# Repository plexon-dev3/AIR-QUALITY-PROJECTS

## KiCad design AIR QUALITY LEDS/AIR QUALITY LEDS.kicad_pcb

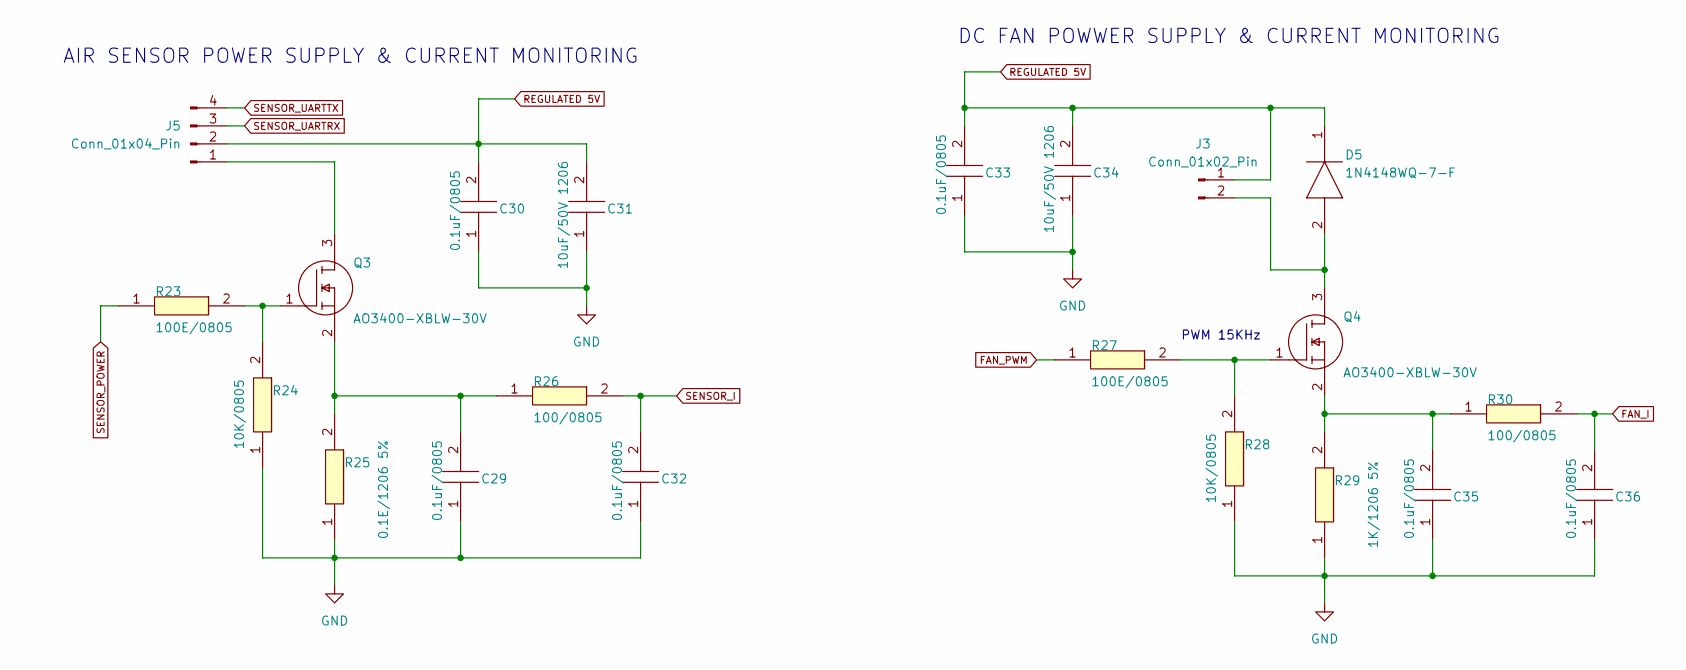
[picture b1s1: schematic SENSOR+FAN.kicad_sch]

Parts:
C29, C30, C32, C33, C35, C36: 0.1uF/0805; C_0805_2012Metric; MANUFACTURER_PART_NUMBER C0805C100F1GACAUTO
C31, C34: 10uF/50V 1206; C_1206_3216Metric; MANUFACTURER_PART_NUMBER C1206C221F5GACAUTO; MOUSER PART NUMBER 80-C1206C221F5GAUTO
D5: 1N4148WQ-7-F; SOD3716X145N; MANUFACTURER_PART_NUMBER 1N4148WQ-7-F; MOUSER PART NUMBER 621-1N4148WQ-7-F
J3: Conn_01x02_Pin; PinSocket_1x02_P2.54mm_Vertical
J5: Conn_01x04_Pin; Hirose_DF13-04P-1.25DSA_1x04_P1.25mm_Vertical
Q3, Q4: AO3400-XBLW-30V; SOT95P237X112-3N; MANUFACTURER_PART_NUMBER IRLML6344TRPBF; MOUSER PART NUMBER 942-IRLML6344TRPBF
R23, R27: 100E/0805; R_0805_2012Metric; MANUFACTURER_PART_NUMBER CMP0805QFX-1001ELF; MOUSER PART NUMBER 652-CMP0805QFX-1001E
R24, R28: 10K/0805; R_0805_2012Metric; MANUFACTURER_PART_NUMBER CMP0805QFX-1001ELF; MOUSER PART NUMBER 652-CMP0805QFX-1001E
R25: 0.1E/1206 5%; R_1206_3216Metric; MANUFACTURER_PART_NUMBER CR1206-FX-16R2ELF; MOUSER PART NUMBER 652-CR1206FX-16R2ELF
R26, R30: 100/0805; R_0805_2012Metric; MANUFACTURER_PART_NUMBER CMP0805QFX-1001ELF; MOUSER PART NUMBER 652-CMP0805QFX-1001E
R29: 1K/1206 5%; R_1206_3216Metric; MANUFACTURER_PART_NUMBER CR1206-FX-16R2ELF; MOUSER PART NUMBER 652-CR1206FX-16R2ELF

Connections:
FAN_I: C36.2, R30.2; also elsewhere on the board
FAN_PWM: R27.1; also elsewhere on the board
GND: C29.1, C30.1, C31.1, C32.1, C33.1, C34.1, C35.1, C36.1, R24.1, R25.1, R28.1, R29.1; also elsewhere on the board
unnamed: D5.2 (A), J3.2, Q4.3 (D)
unnamed: J5.1, Q3.3 (D)
unnamed: Q3.1 (G), R23.2, R24.2
unnamed: C29.2, Q3.2 (S), R25.2, R26.1
unnamed: Q4.1 (G), R27.2, R28.2
unnamed: C35.2, Q4.2 (S), R29.2, R30.1
REGULATED 5V: C30.2, C31.2, C33.2, C34.2, D5.1 (K), J3.1, J5.2; also elsewhere on the board
SENSOR_I: C32.2, R26.2; also elsewhere on the board
SENSOR_POWER: R23.1; also elsewhere on the board
SENSOR_UARTRX: J5.3; also elsewhere on the board
SENSOR_UARTTX: J5.4; also elsewhere on the board

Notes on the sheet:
AIR SENSOR POWER SUPPLY & CURRENT MONITORING
DC FAN POWWER SUPPLY & CURRENT MONITORING
PWM 15KHz

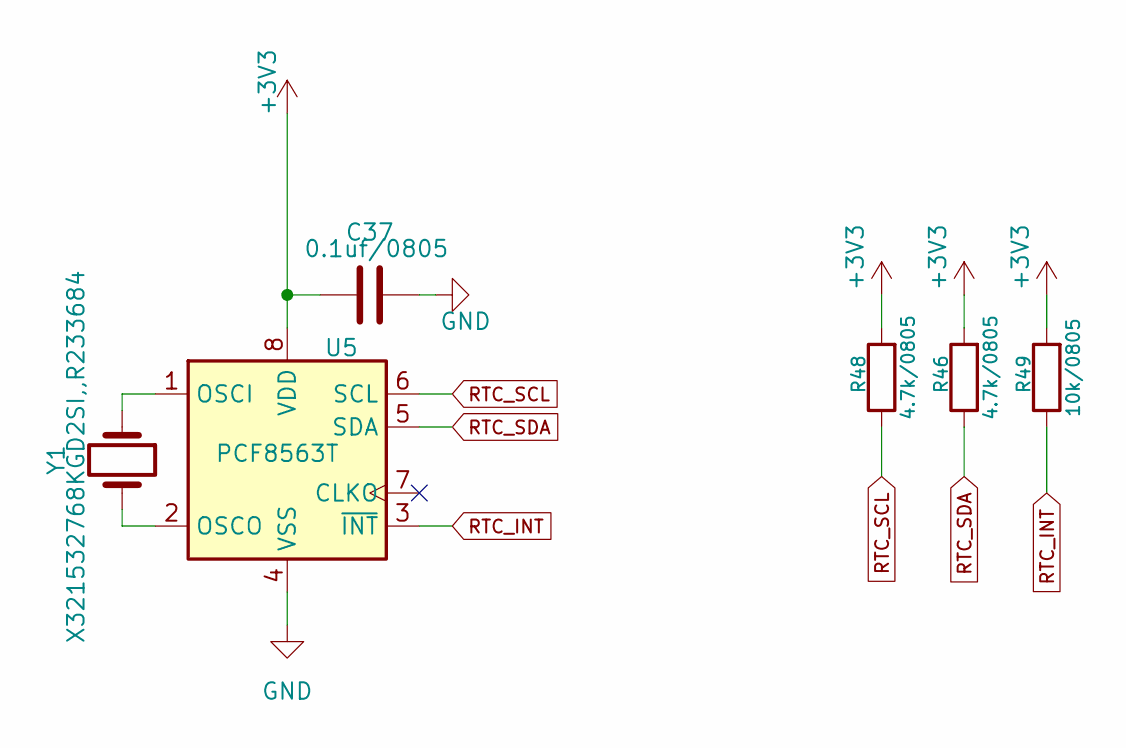
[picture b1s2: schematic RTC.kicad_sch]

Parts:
C37: 0.1uf/0805; C_0805_2012Metric
R46, R48: 4.7k/0805; R_0805_2012Metric
R49: 10k/0805; R_0805_2012Metric
U5: PCF8563T; SO-8_3.9x4.9mm_P1.27mm
Y1: X321532768KGD2SI,,R233684; Crystal_SMD_MicroCrystal_CC7V-T1A-2Pin_3.2x1.5mm

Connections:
+3V3: C37.1, R46.2, R48.2, R49.2, U5.8 (VDD); also elsewhere on the board
GND: C37.2, U5.4 (VSS); also elsewhere on the board
unnamed: U5.1 (OSCI), Y1.1
unnamed: U5.2 (OSCO), Y1.2
RTC_INT: R49.1, U5.3 (~INT); also elsewhere on the board
RTC_SCL: R48.1, U5.6 (SCL); also elsewhere on the board
RTC_SDA: R46.1, U5.5 (SDA); also elsewhere on the board

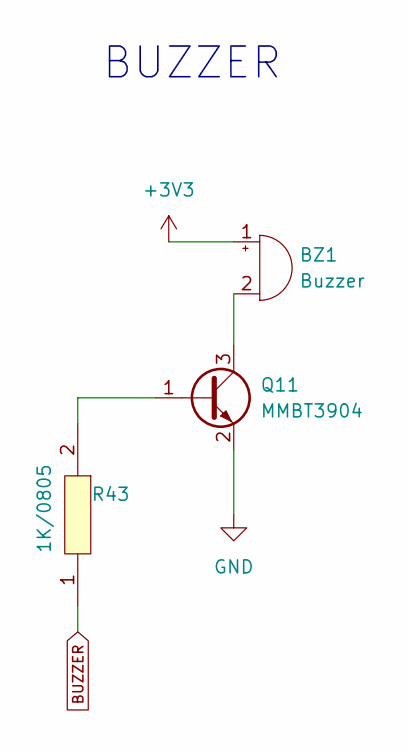
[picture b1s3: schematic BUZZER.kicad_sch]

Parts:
BZ1: Buzzer; Buzzer_12x9.5RM7.6
Q11: MMBT3904; SOT-23
R43: 1K/0805; R_0805_2012Metric; MANUFACTURER_PART_NUMBER CMP0805QFX-1001ELF; MOUSER PART NUMBER 652-CMP0805QFX-1001E

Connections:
+3V3: BZ1.1 (+); also elsewhere on the board
BUZZER: R43.1; also elsewhere on the board
GND: Q11.2 (E); also elsewhere on the board
unnamed: BZ1.2 (-), Q11.3 (C)
unnamed: Q11.1 (B), R43.2

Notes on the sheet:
BUZZER

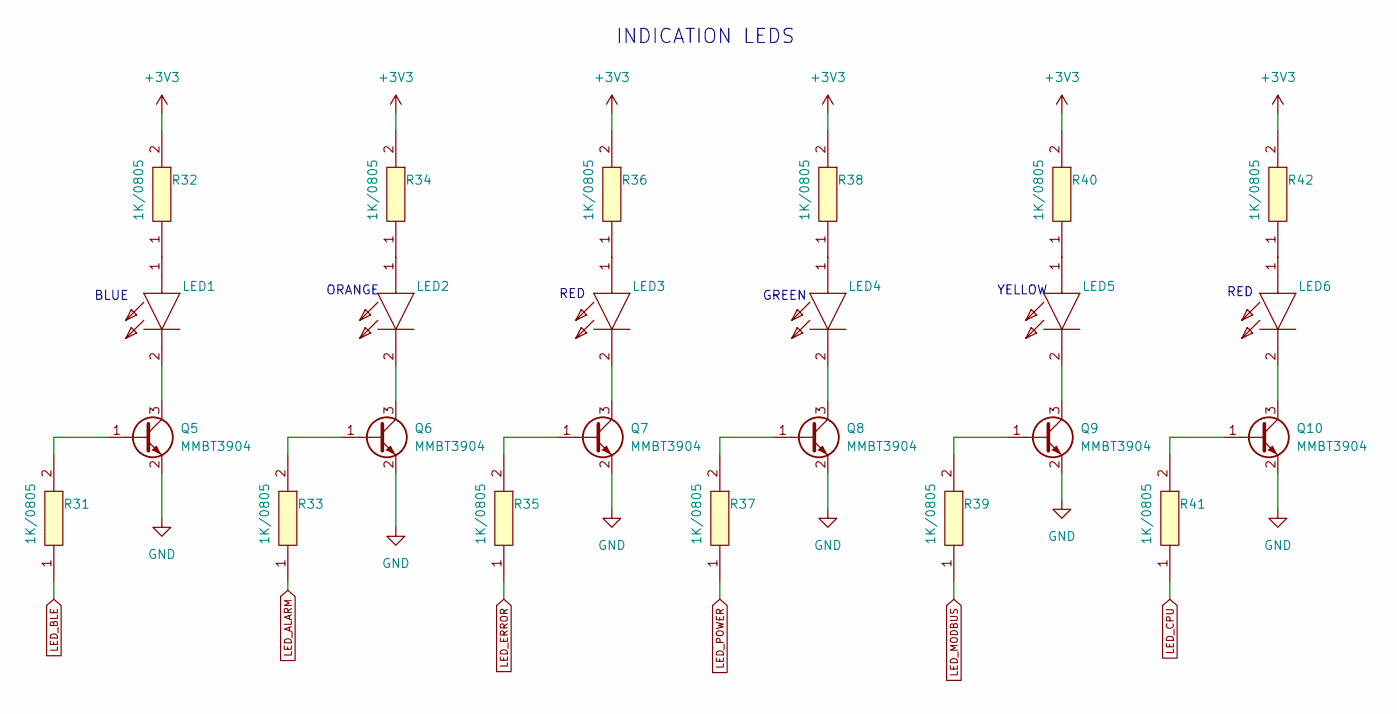
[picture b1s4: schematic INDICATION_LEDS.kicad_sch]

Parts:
LED1, LED2, LED3, LED4, LED5, LED6: LED_D5.0mm; MANUFACTURER_PART_NUMBER 151051BS04000; MOUSER PART NUMBER 710-151051BS04000
Q5, Q6, Q7, Q8, Q9, Q10: MMBT3904; SOT-23
R31, R32, R33, R34, R35, R36, R37, R38, R39, R40, R41, R42: 1K/0805; R_0805_2012Metric; MANUFACTURER_PART_NUMBER CMP0805QFX-1001ELF; MOUSER PART NUMBER 652-CMP0805QFX-1001E

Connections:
+3V3: R32.2, R34.2, R36.2, R38.2, R40.2, R42.2; also elsewhere on the board
GND: Q5.2 (E), Q6.2 (E), Q7.2 (E), Q8.2 (E), Q9.2 (E), Q10.2 (E); also elsewhere on the board
LED_ALARM: R33.1; also elsewhere on the board
LED_BLE: R31.1; also elsewhere on the board
LED_CPU: R41.1; also elsewhere on the board
LED_ERROR: R35.1; also elsewhere on the board
LED_MODBUS: R39.1; also elsewhere on the board
LED_POWER: R37.1; also elsewhere on the board
unnamed: LED1.1 (A), R32.1
unnamed: LED1.2 (K), Q5.3 (C)
unnamed: LED2.1 (A), R34.1
unnamed: LED2.2 (K), Q6.3 (C)
unnamed: LED3.1 (A), R36.1
unnamed: LED3.2 (K), Q7.3 (C)
unnamed: LED4.1 (A), R38.1
unnamed: LED4.2 (K), Q8.3 (C)
unnamed: LED5.1 (A), R40.1
unnamed: LED5.2 (K), Q9.3 (C)
unnamed: LED6.1 (A), R42.1
unnamed: LED6.2 (K), Q10.3 (C)
unnamed: Q5.1 (B), R31.2
unnamed: Q6.1 (B), R33.2
unnamed: Q7.1 (B), R35.2
unnamed: Q8.1 (B), R37.2
unnamed: Q9.1 (B), R39.2
unnamed: Q10.1 (B), R41.2

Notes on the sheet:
BLUE
RED
ORANGE
YELLOW
GREEN
INDICATION LEDS

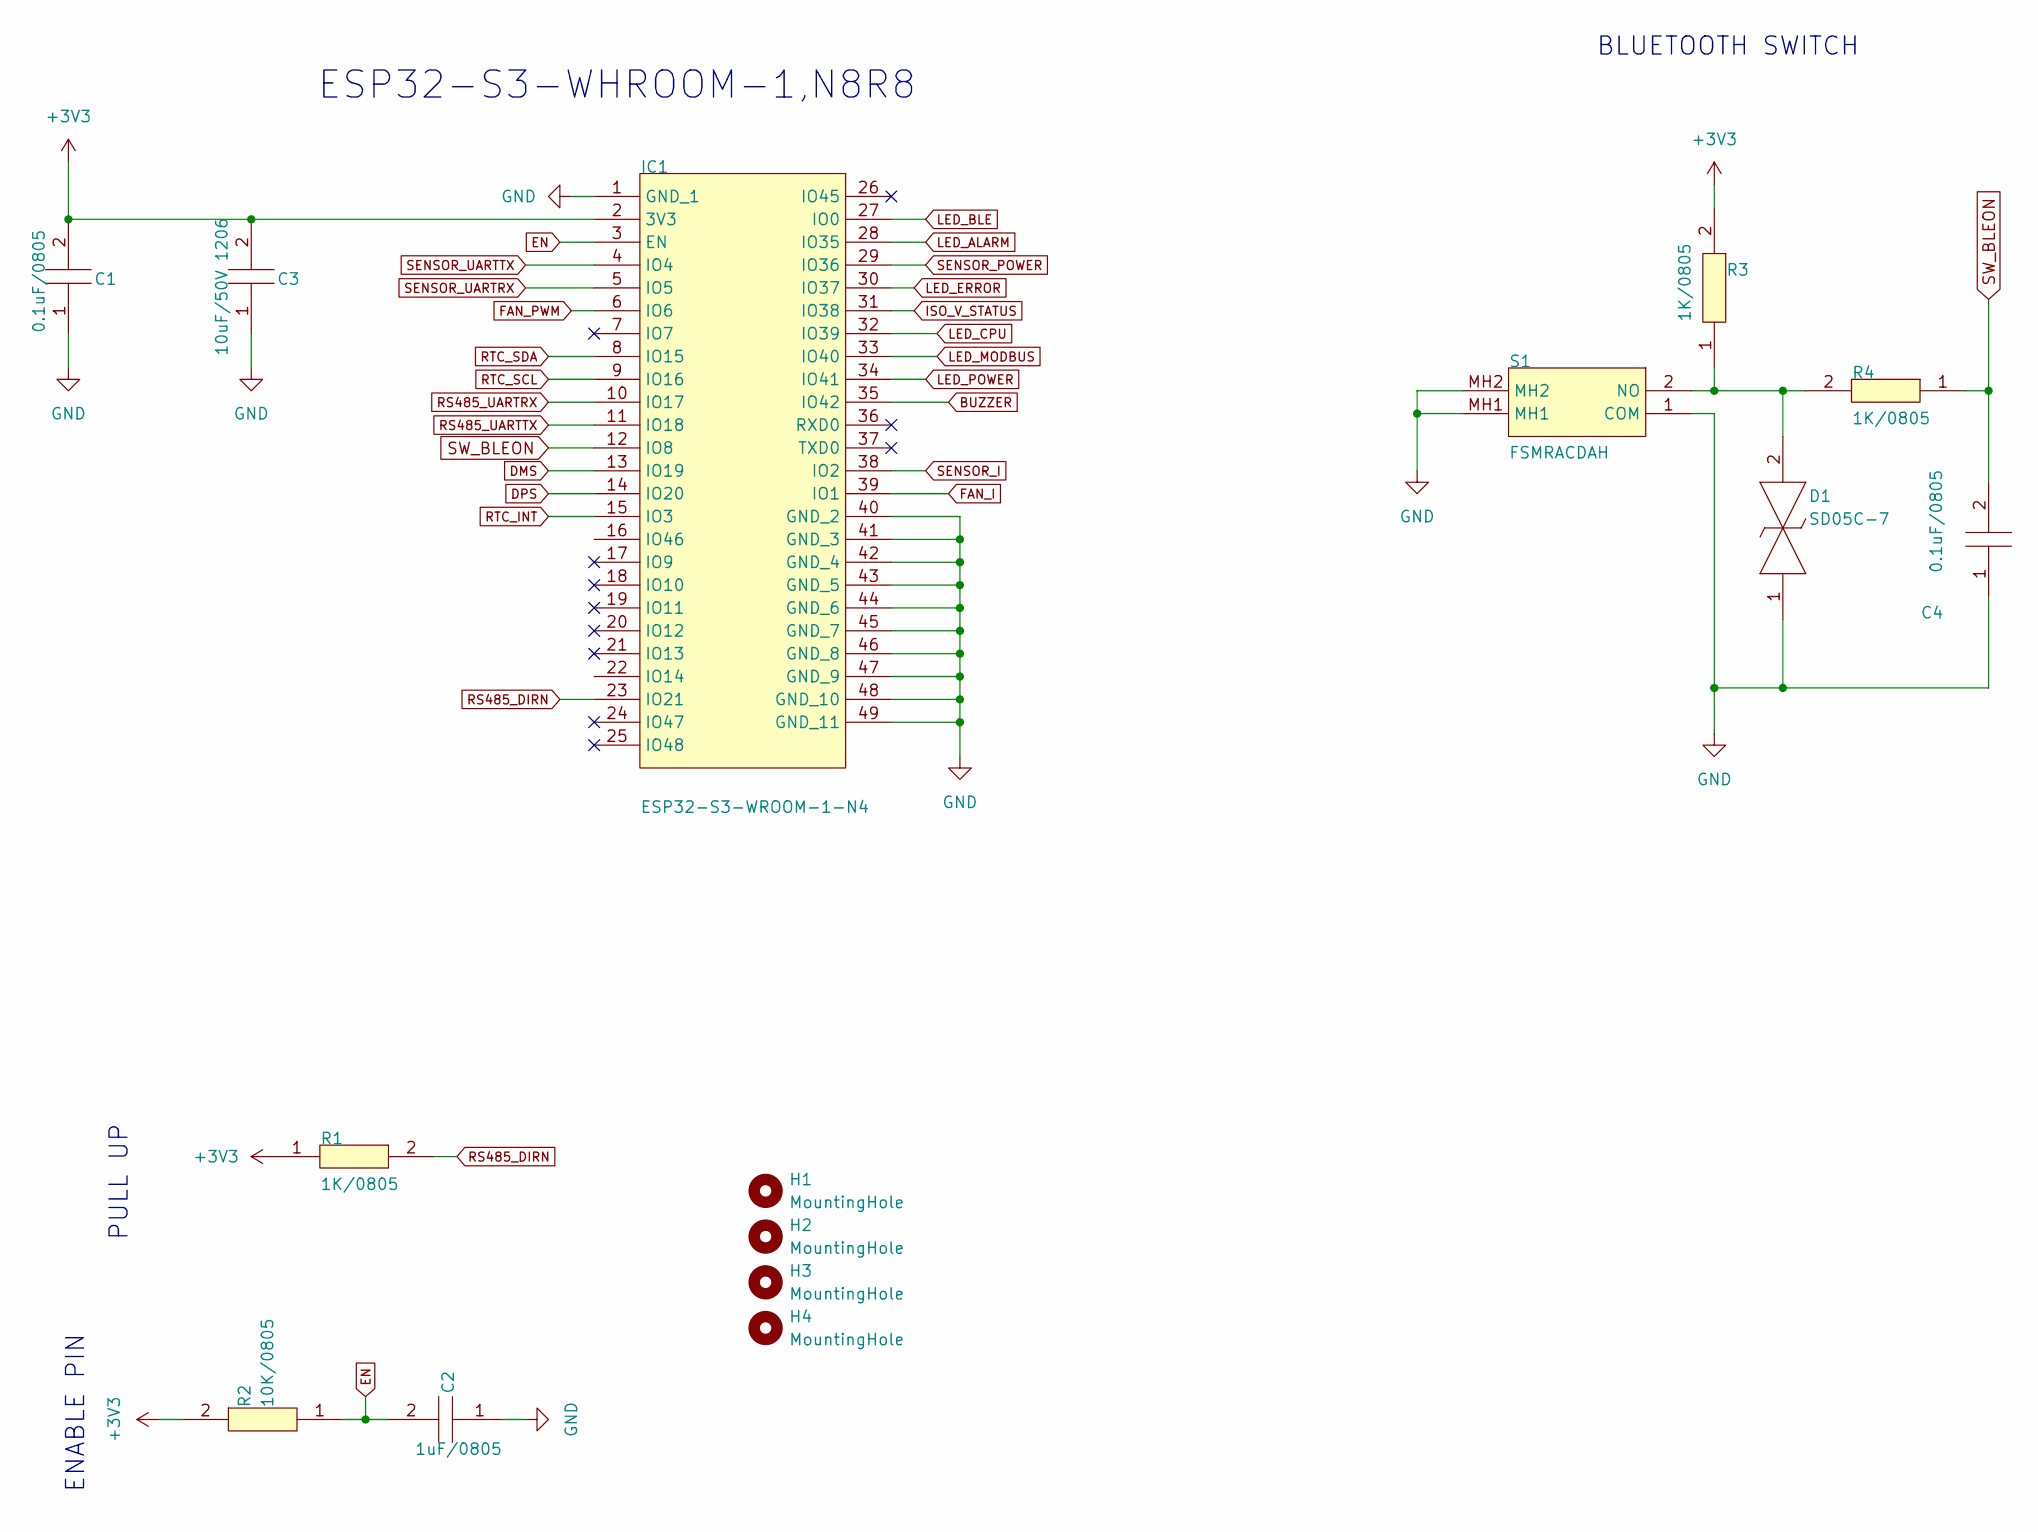
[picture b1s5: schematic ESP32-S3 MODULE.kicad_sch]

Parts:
C1, C4: 0.1uF/0805; C_0805_2012Metric; MANUFACTURER_PART_NUMBER C0805C100F1GACAUTO
C2: 1uF/0805; C_0805_2012Metric; MANUFACTURER_PART_NUMBER C0805C100F1GACAUTO
C3: 10uF/50V 1206; C_1206_3216Metric; MANUFACTURER_PART_NUMBER C1206C221F5GACAUTO; MOUSER PART NUMBER 80-C1206C221F5GAUTO
D1: SD05C-7; SOD2513X120N; MANUFACTURER_PART_NUMBER SD05C-7; MOUSER PART NUMBER 621-SD05C-7
H1, H2, H3, H4: MountingHole; MountingHole_3mm
IC1: ESP32-S3-WROOM-1-N4; ESP32S3WROOM1N8R8; MANUFACTURER_PART_NUMBER ESP32-S3-WROOM-1-N4; MOUSER PART NUMBER 356-ESP32-S3WROOM1N4
R1, R3, R4: 1K/0805; R_0805_2012Metric; MANUFACTURER_PART_NUMBER CMP0805QFX-1001ELF; MOUSER PART NUMBER 652-CMP0805QFX-1001E
R2: 10K/0805; R_0805_2012Metric; MANUFACTURER_PART_NUMBER CMP0805QFX-1001ELF; MOUSER PART NUMBER 652-CMP0805QFX-1001E
S1: FSMRACDAH; MANUFACTURER_PART_NUMBER FSMRACDAH; MOUSER PART NUMBER 506-FSMRACDAH

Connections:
+3V3: C1.2, C3.2, IC1.2 (3V3), R1.1, R2.2, R3.2; also elsewhere on the board
BUZZER: IC1.35 (IO42); also elsewhere on the board
DMS: IC1.13 (IO19); also elsewhere on the board
DPS: IC1.14 (IO20); also elsewhere on the board
EN: C2.2, IC1.3 (EN), R2.1
FAN_I: IC1.39 (IO1); also elsewhere on the board
FAN_PWM: IC1.6 (IO6); also elsewhere on the board
GND: C1.1, C2.1, C3.1, C4.1, D1.1, IC1.1 (GND_1), IC1.40 (GND_2), IC1.41 (GND_3), IC1.42 (GND_4), IC1.43 (GND_5), IC1.44 (GND_6), IC1.45 (GND_7), IC1.46 (GND_8), IC1.47 (GND_9), IC1.48 (GND_10), IC1.49 (GND_11), S1.1 (COM), S1.MH1, S1.MH2; also elsewhere on the board
ISO_V_STATUS: IC1.31 (IO38); also elsewhere on the board
LED_ALARM: IC1.28 (IO35); also elsewhere on the board
LED_BLE: IC1.27 (IO0); also elsewhere on the board
LED_CPU: IC1.32 (IO39); also elsewhere on the board
LED_ERROR: IC1.30 (IO37); also elsewhere on the board
LED_MODBUS: IC1.33 (IO40); also elsewhere on the board
LED_POWER: IC1.34 (IO41); also elsewhere on the board
unnamed: D1.2, R3.1, R4.2, S1.2 (NO)
RS485_DIRN: IC1.23 (IO21), R1.2; also elsewhere on the board
RS485_UARTRX: IC1.10 (IO17); also elsewhere on the board
RS485_UARTTX: IC1.11 (IO18); also elsewhere on the board
RTC_INT: IC1.15 (IO3); also elsewhere on the board
RTC_SCL: IC1.9 (IO16); also elsewhere on the board
RTC_SDA: IC1.8 (IO15); also elsewhere on the board
SENSOR_I: IC1.38 (IO2); also elsewhere on the board
SENSOR_POWER: IC1.29 (IO36); also elsewhere on the board
SENSOR_UARTRX: IC1.5 (IO5); also elsewhere on the board
SENSOR_UARTTX: IC1.4 (IO4); also elsewhere on the board
SW_BLEON: C4.2, IC1.12 (IO8), R4.1

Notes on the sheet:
PULL UP
BLUETOOTH SWITCH
ENABLE PIN
ESP32-S3-WHROOM-1,N8R8

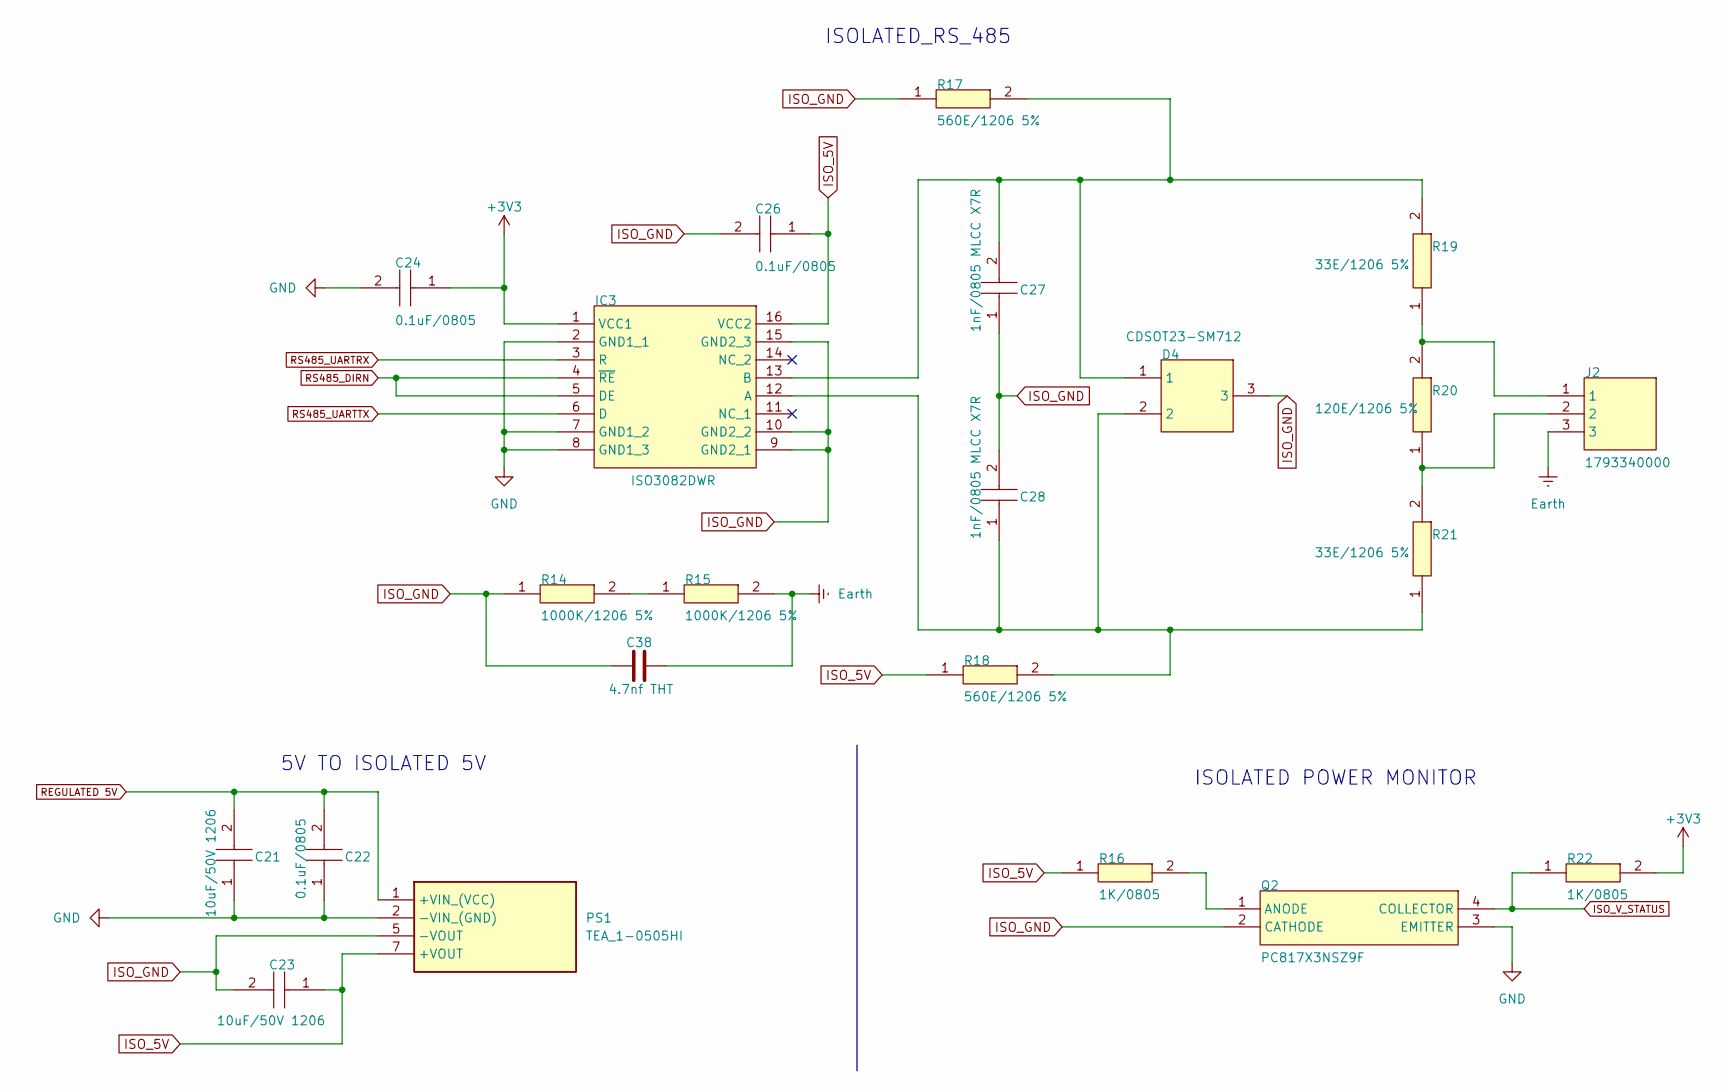
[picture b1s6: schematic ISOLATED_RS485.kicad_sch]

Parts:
C21, C23: 10uF/50V 1206; C_1206_3216Metric; MANUFACTURER_PART_NUMBER C1206C221F5GACAUTO; MOUSER PART NUMBER 80-C1206C221F5GAUTO
C22, C24, C26: 0.1uF/0805; C_0805_2012Metric; MANUFACTURER_PART_NUMBER C0805C100F1GACAUTO
C27, C28: 1nF/0805 MLCC X7R; C_0805_2012Metric; MANUFACTURER_PART_NUMBER C0805C100F1GACAUTO
C38: 4.7nf THT; C_Disc_D3.0mm_W1.6mm_P2.50mm
D4: CDSOT23-SM712; SOT95P230X117-3N; MANUFACTURER_PART_NUMBER CDSOT23-SM712; MOUSER PART NUMBER 652-CDSOT23-SM712
IC3: ISO3082DWR; SOIC127P1030X265-16N; MANUFACTURER_PART_NUMBER ISO3082DWR; MOUSER PART NUMBER 595-ISO3082DWR
J2: 1793340000; MANUFACTURER_PART_NUMBER 1793340000; MOUSER PART NUMBER 470-1793340000
PS1: TEA_1-0505HI; TEA10505HI; Mouser Part Number 495-TEA1-0505HI
Q2: PC817X3NSZ9F; DIP762W60P254L460H450Q4N; MANUFACTURER_PART_NUMBER PC817X3NSZ9F; MOUSER PART NUMBER 852-PC817X3NSZ9F
R14, R15: 1000K/1206 5%; R_1206_3216Metric; MANUFACTURER_PART_NUMBER CR1206-FX-16R2ELF; MOUSER PART NUMBER 652-CR1206FX-16R2ELF
R16, R22: 1K/0805; R_0805_2012Metric; MANUFACTURER_PART_NUMBER CMP0805QFX-1001ELF; MOUSER PART NUMBER 652-CMP0805QFX-1001E
R17, R18: 560E/1206 5%; R_1206_3216Metric; MANUFACTURER_PART_NUMBER CR1206-FX-16R2ELF; MOUSER PART NUMBER 652-CR1206FX-16R2ELF
R19, R21: 33E/1206 5%; R_1206_3216Metric; MANUFACTURER_PART_NUMBER CR1206-FX-16R2ELF; MOUSER PART NUMBER 652-CR1206FX-16R2ELF
R20: 120E/1206 5%; R_1206_3216Metric; MANUFACTURER_PART_NUMBER CR1206-FX-16R2ELF; MOUSER PART NUMBER 652-CR1206FX-16R2ELF

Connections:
+3V3: C24.1, IC3.1 (VCC1), R22.2; also elsewhere on the board
Earth: C38.2, J2.3, R15.2
GND: C21.1, C22.1, C24.2, IC3.2 (GND1_1), IC3.7 (GND1_2), IC3.8 (GND1_3), PS1.2 (-VIN_(GND)), Q2.3 (EMITTER); also elsewhere on the board
ISO_5V: C23.1, C26.1, IC3.16 (VCC2), PS1.7 (+VOUT), R16.1, R18.1
ISO_GND: C23.2, C26.2, C27.1, C28.2, C38.1, D4.3, IC3.9 (GND2_1), IC3.10 (GND2_2), IC3.15 (GND2_3), PS1.5 (-VOUT), Q2.2 (CATHODE), R14.1, R17.1
ISO_V_STATUS: Q2.4 (COLLECTOR), R22.1; also elsewhere on the board
unnamed: C28.1, D4.2, IC3.12 (A), R18.2, R21.1
unnamed: C27.2, D4.1, IC3.13 (B), R17.2, R19.2
unnamed: J2.1, R19.1, R20.2
unnamed: J2.2, R20.1, R21.2
unnamed: Q2.1 (ANODE), R16.2
unnamed: R14.2, R15.1
REGULATED 5V: C21.2, C22.2, PS1.1 (+VIN_(VCC)); also elsewhere on the board
RS485_DIRN: IC3.4 (~RE), IC3.5 (DE); also elsewhere on the board
RS485_UARTRX: IC3.3 (R); also elsewhere on the board
RS485_UARTTX: IC3.6 (D); also elsewhere on the board

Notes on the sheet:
5V TO ISOLATED 5V
ISOLATED_RS_485
ISOLATED POWER MONITOR

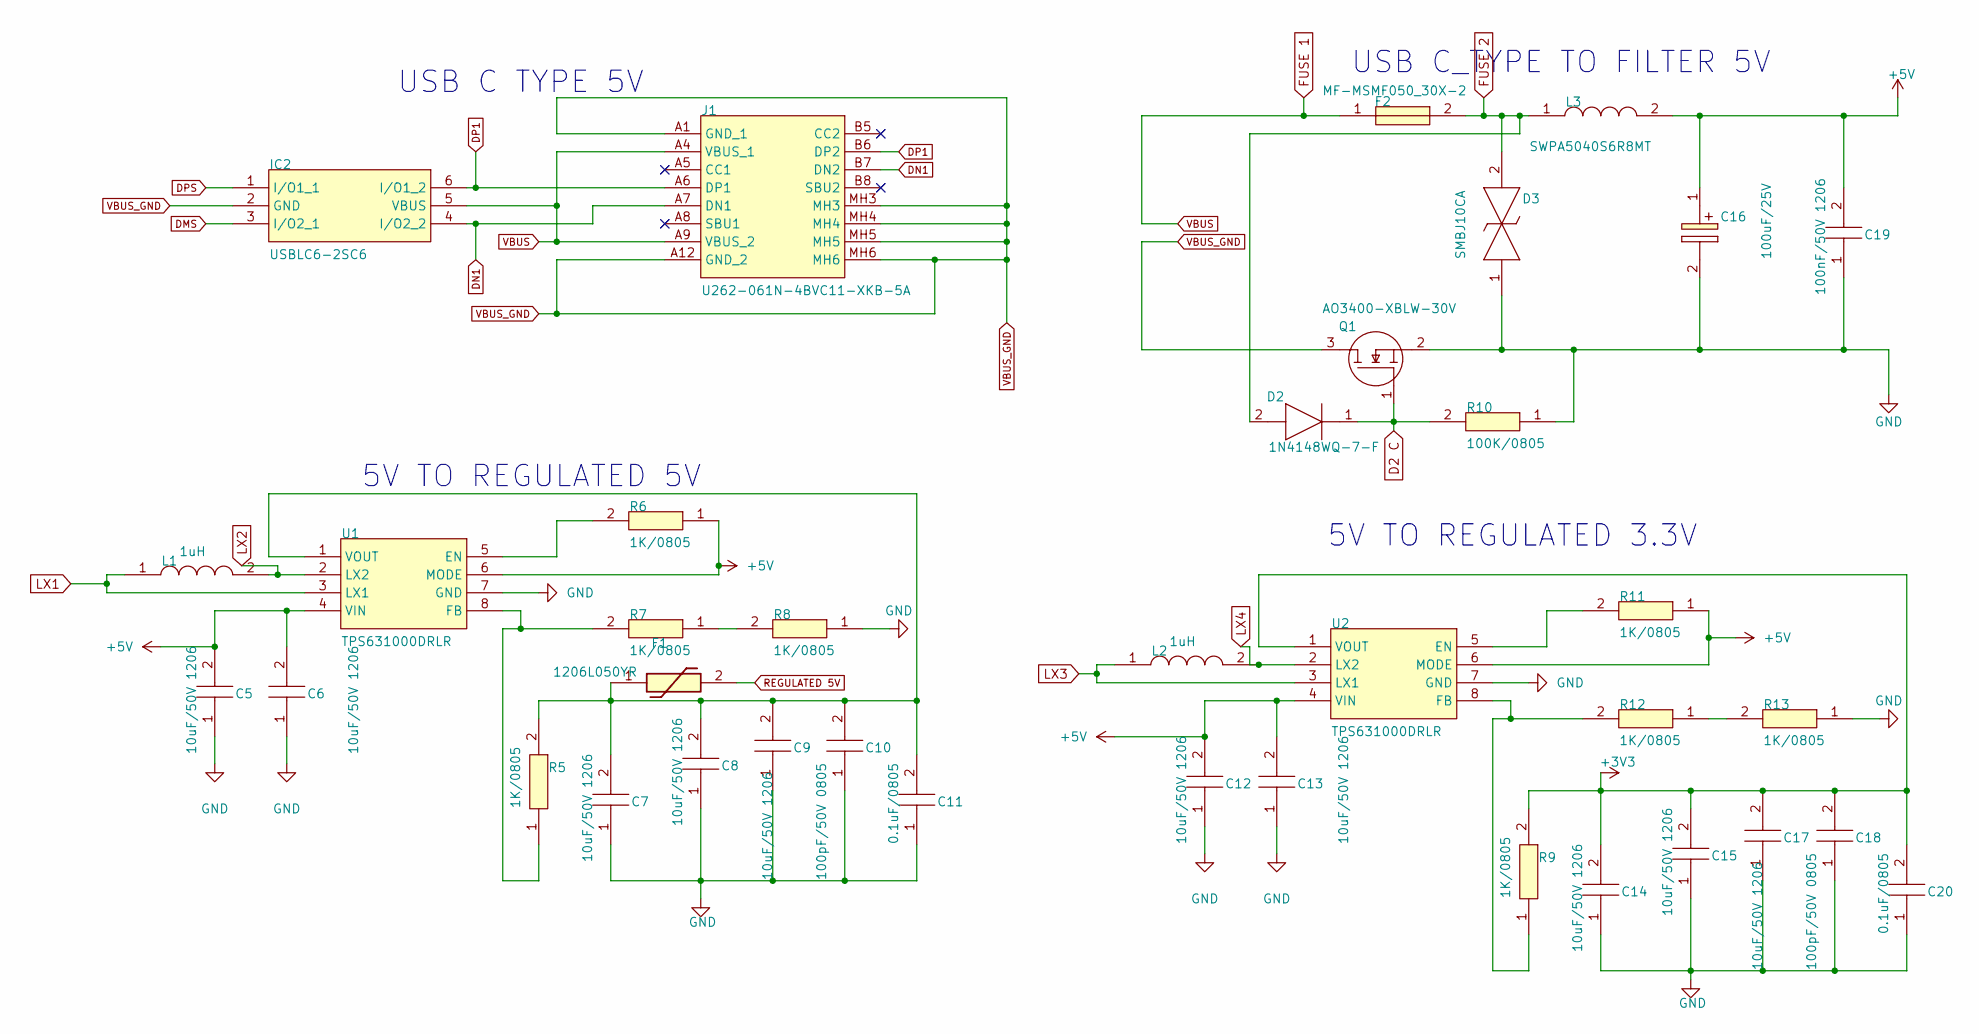
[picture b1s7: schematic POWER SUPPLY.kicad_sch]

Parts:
C5, C6, C7, C8, C9, C12, C13, C14, C15, C17: 10uF/50V 1206; C_1206_3216Metric; MANUFACTURER_PART_NUMBER C1206C221F5GACAUTO; MOUSER PART NUMBER 80-C1206C221F5GAUTO
C10, C18: 100pF/50V 0805; C_0805_2012Metric; MANUFACTURER_PART_NUMBER C0805C100F1GACAUTO
C11, C20: 0.1uF/0805; C_0805_2012Metric; MANUFACTURER_PART_NUMBER C0805C100F1GACAUTO
C16: 100uF/25V; CAPPRD200W50D500H1250; MANUFACTURER_PART_NUMBER ESK106M035AC3AA; MOUSER PART NUMBER 80-ESK106M035AC3AA
C19: 100nF/50V 1206; C_1206_3216Metric; MANUFACTURER_PART_NUMBER C1206C221F5GACAUTO; MOUSER PART NUMBER 80-C1206C221F5GAUTO
D2: 1N4148WQ-7-F; SOD3716X145N; MANUFACTURER_PART_NUMBER 1N4148WQ-7-F; MOUSER PART NUMBER 621-1N4148WQ-7-F
D3: SMBJ10CA; DIONM5436X261N; MANUFACTURER_PART_NUMBER SMBJ28CA; MOUSER PART NUMBER 576-SMBJ28CA
F1: 1206L050YR; 1206L05015YR; Mouser Part Number 576-1206L050YR
F2: MF-MSMF050_30X-2; FUSC4632X85N; MANUFACTURER_PART_NUMBER MF-MSMF050/30X-2; MOUSER PART NUMBER 652-MF-MSMF050/30X-2
IC2: USBLC6-2SC6; SOT95P280X145-6N; MANUFACTURER_PART_NUMBER USBLC6-2SC6; MOUSER PART NUMBER 511-USBLC6-2SC6
J1: U262-061N-4BVC11-XKB-5A; USB480003A; MANUFACTURER_PART_NUMBER USB4800-03-A; MOUSER PART NUMBER 640-USB4800-03-A
L1, L2: 1uH; DFE2HCAH1R0MJ0L; MANUFACTURER_PART_NUMBER DFE252012P-1R0M=P2; MOUSER PART NUMBER 81-DFE252012P-1R0MP2
L3: SWPA5040S6R8MT; 74404054330; MANUFACTURER_PART_NUMBER 74404054330; MOUSER PART NUMBER 710-74404054330
Q1: AO3400-XBLW-30V; SOT95P237X112-3N; MANUFACTURER_PART_NUMBER IRLML6344TRPBF; MOUSER PART NUMBER 942-IRLML6344TRPBF
R5, R6, R7, R8, R9, R11, R12, R13: 1K/0805; R_0805_2012Metric; MANUFACTURER_PART_NUMBER CMP0805QFX-1001ELF; MOUSER PART NUMBER 652-CMP0805QFX-1001E
R10: 100K/0805; R_0805_2012Metric; MANUFACTURER_PART_NUMBER CMP0805QFX-1001ELF; MOUSER PART NUMBER 652-CMP0805QFX-1001E
U1, U2: TPS631000DRLR; SOTFL50P160X60-8N; MANUFACTURER_PART_NUMBER TPS631000DRLR; MOUSER PART NUMBER 595-TPS631000DRLR

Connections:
+3V3: C14.2, C15.2, C17.2, C18.2, C20.2, R9.2, U2.1 (VOUT); also elsewhere on the board
+5V: C5.2, C6.2, C12.2, C13.2, C16.1 (+), C19.2, L3.2, R6.1, R11.1, U1.4 (VIN), U1.6 (MODE), U2.4 (VIN), U2.6 (MODE)
D2 C: D2.1 (K), Q1.1 (G), R10.2
DMS: IC2.3 (I/O2_1); also elsewhere on the board
DN1: IC2.4 (I/O2_2), J1.A7 (DN1), J1.B7 (DN2)
DP1: IC2.6 (I/O1_2), J1.A6 (DP1), J1.B6 (DP2)
DPS: IC2.1 (I/O1_1); also elsewhere on the board
FUSE 1: F2.1, IC2.5 (VBUS), J1.A4 (VBUS_1), J1.A9 (VBUS_2)
FUSE 2: D2.2 (A), D3.2, F2.2, L3.1
GND: C5.1, C6.1, C7.1, C8.1, C9.1, C10.1, C11.1, C12.1, C13.1, C14.1, C15.1, C16.2 (-), C17.1, C18.1, C19.1, C20.1, D3.1, Q1.2 (S), R8.1, R10.1, R13.1, U1.7 (GND), U2.7 (GND); also elsewhere on the board
LX1: L1.1, U1.3 (LX1)
LX2: L1.2, U1.2 (LX2)
LX3: L2.1, U2.3 (LX1)
LX4: L2.2, U2.2 (LX2)
unnamed: R7.1, R8.2
unnamed: R12.1, R13.2
unnamed: R6.2, U1.5 (EN)
unnamed: R5.1, R7.2, U1.8 (FB)
unnamed: C7.2, C8.2, C9.2, C10.2, C11.2, F1.1, R5.2, U1.1 (VOUT)
unnamed: R11.2, U2.5 (EN)
unnamed: R9.1, R12.2, U2.8 (FB)
REGULATED 5V: F1.2; also elsewhere on the board
VBUS_GND: IC2.2 (GND), J1.A1 (GND_1), J1.A12 (GND_2), J1.MH3, J1.MH4, J1.MH5, J1.MH6, Q1.3 (D)

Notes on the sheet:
5V TO REGULATED 5V
USB C_TYPE TO FILTER 5V
5V TO REGULATED 3.3V
USB C TYPE 5V

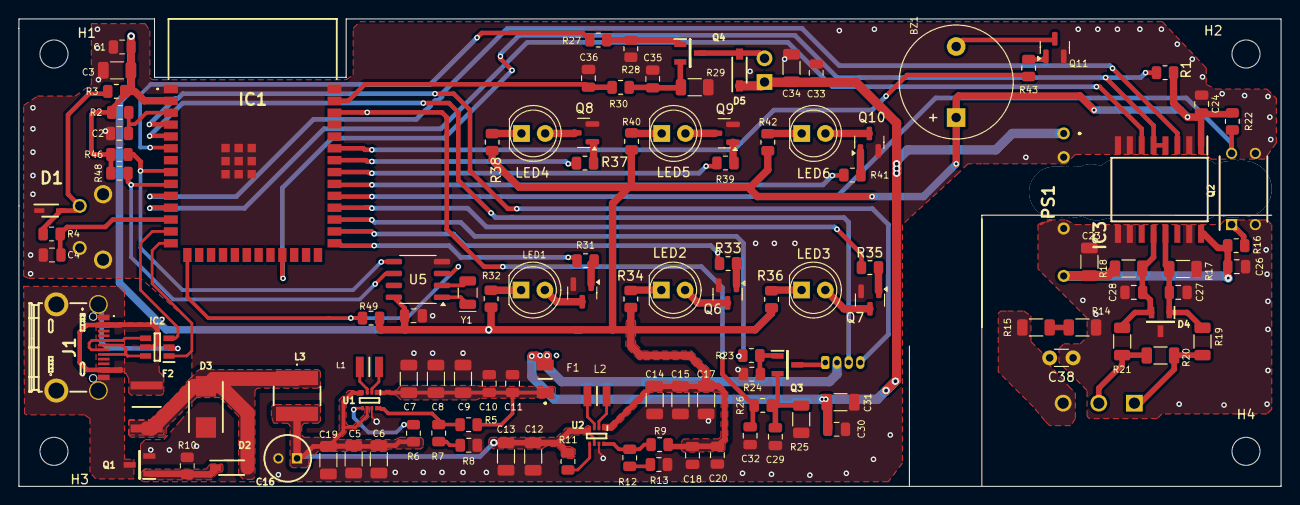
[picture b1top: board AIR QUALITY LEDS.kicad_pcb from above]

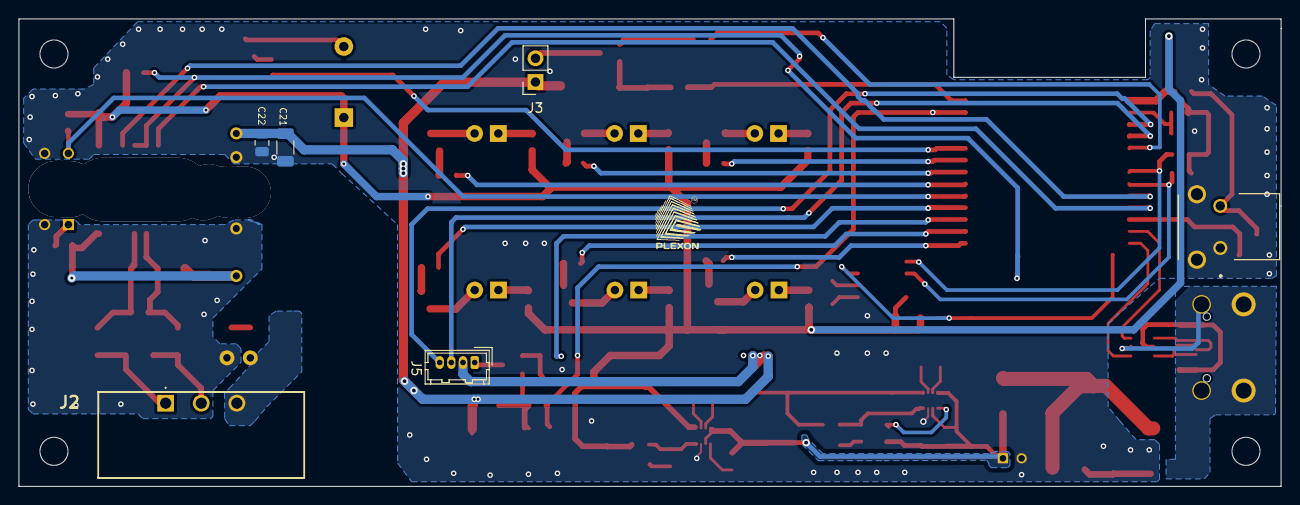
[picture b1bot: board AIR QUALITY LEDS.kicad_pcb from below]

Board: 2 copper layers, 135.0 x 50.0 mm, 128 parts (6 on the bottom side), 83 nets.

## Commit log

2026-05-13 Removed gerber files
